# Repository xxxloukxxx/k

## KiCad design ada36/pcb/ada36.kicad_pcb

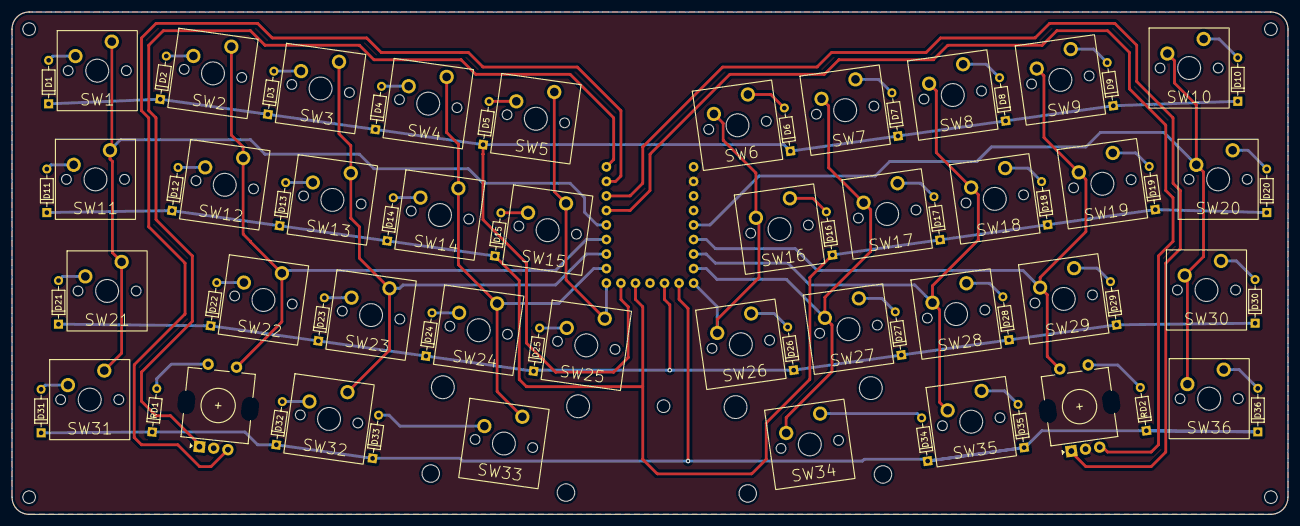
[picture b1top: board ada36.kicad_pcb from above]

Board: 2 copper layers, 223.1 x 87.8 mm, 82 parts (1 on the bottom side), 57 nets.

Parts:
D1, D2, D3, D4, D5, D6, D7, D8, D9, D10, D11, D12, D13, D14, D15, D16, D17, D18, D19, D20, D21, D22, D23, D24, D25, D26, D27, D28, D29, D30, D31, D32, D33, D34, D35, D36: DIODE; Diode
H1, H2, H3, H4, H5: MountingHole; MountingHole_2.2mm_M2
R1, R2: EC11-MX-Alps; RotaryEncoder_EC11
RD1, RD2: DIODE; Diode
SW1, SW2, SW3, SW4, SW5, SW6, SW7, SW8, SW9, SW10, SW11, SW12, SW13, SW14, SW15, SW16, SW17, SW18, SW19, SW20, SW21, SW22, SW23, SW24, SW25, SW26, SW27, SW28, SW29, SW30, SW31, SW32, SW35, SW36: key; MX-5pin
SW33, SW34: key; MX-5pin_stab_rev
U1: RP2040

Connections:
GND: R1.C, R2.C, U1.21
unnamed: D1.2, SW1.2
unnamed: D2.2, SW2.2
unnamed: D3.2, SW3.2
unnamed: D4.2, SW4.2
unnamed: D5.2, SW5.2
unnamed: D6.2, SW6.1
unnamed: D7.2, SW7.1
unnamed: D8.2, SW8.1
unnamed: D9.2, SW9.1
unnamed: D10.2, SW10.1
unnamed: D11.2, SW11.2
unnamed: D12.2, SW12.2
unnamed: D13.2, SW13.2
unnamed: D14.2, SW14.2
unnamed: D15.2, SW15.2
unnamed: D16.2, SW16.1
unnamed: D17.2, SW17.1
unnamed: D18.2, SW18.1
unnamed: D19.2, SW19.1
unnamed: D20.2, SW20.1
unnamed: D21.2, SW21.2
unnamed: D22.2, SW22.2
unnamed: D23.2, SW23.2
unnamed: D24.2, SW24.2
unnamed: D25.2, SW25.2
unnamed: D26.2, SW26.1
unnamed: D27.2, SW27.1
unnamed: D28.2, SW28.1
unnamed: D29.2, SW29.1
unnamed: D30.2, SW30.1
unnamed: D31.2, SW31.2
unnamed: D32.2, SW32.2
unnamed: D33.2, SW33.2
unnamed: D34.2, SW34.1
unnamed: D35.2, SW35.1
unnamed: D36.2, SW36.1
unnamed: R1.1, RD1.2
unnamed: R1.A, U1.0
unnamed: R1.B, U1.1
unnamed: R2.2, RD2.2
unnamed: R2.A, U1.2
unnamed: R2.B, U1.3
c0: SW1.1, SW11.1, SW21.1, SW31.1, U1.4
c1: R1.2, SW2.1, SW12.1, SW22.1, U1.5
c2: SW3.1, SW13.1, SW23.1, SW32.1, U1.6
c3: SW4.1, SW14.1, SW24.1, SW33.1, U1.7
c4: SW5.1, SW15.1, SW25.1, U1.8
c5: SW6.2, SW16.2, SW26.2, U1.14
c6: SW7.2, SW17.2, SW27.2, SW34.2, U1.15
c7: SW8.2, SW18.2, SW28.2, SW35.2, U1.16
c8: R2.1, SW9.2, SW19.2, SW29.2, U1.17
c9: SW10.2, SW20.2, SW30.2, SW36.2, U1.18
l0: D31.1, D32.1, D33.1, D34.1, D35.1, D36.1, RD1.1, RD2.1, U1.13
l1: D21.1, D22.1, D23.1, D24.1, D25.1, D26.1, D27.1, D28.1, D29.1, D30.1, U1.12
l2: D11.1, D12.1, D13.1, D14.1, D15.1, D16.1, D17.1, D18.1, D19.1, D20.1, U1.10
l3: D1.1, D2.1, D3.1, D4.1, D5.1, D6.1, D7.1, D8.1, D9.1, D10.1, U1.9

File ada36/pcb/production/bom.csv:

Designator,Footprint,Quantity,Value,LCSC Part #
"D1, D10, D11, D12, D13, D14, D15, D16, D17, D18, D19, D2, D20, D21, D22, D23, D24, D25, D26, D27, D28, D29, D3, D30, D31, D32, D33, D34, D35, D36, D4, D5, D6, D7, D8, D9, RD1, RD2",Diode,38,Diode,
"H1, H2, H3, H4, H5",MountingHole_2.2mm_M2,5,MountingHole,
"R1, R2",RotaryEncoder_EC11,2,EC11-MX-Alps,
"SW1, SW10, SW11, SW12, SW13, SW14, SW15, SW16, SW17, SW18, SW19, SW2, SW20, SW21, SW22, SW23, SW24, SW25, SW26, SW27, SW28, SW29, SW3, SW30, SW31, SW32, SW35, SW36, SW4, SW5, SW6, SW7, SW8, SW9",MX-5pin,34,key,
"SW33, SW34",MX-5pin_stab_rev,2,key,
U1,RP2040,1,RP2040,

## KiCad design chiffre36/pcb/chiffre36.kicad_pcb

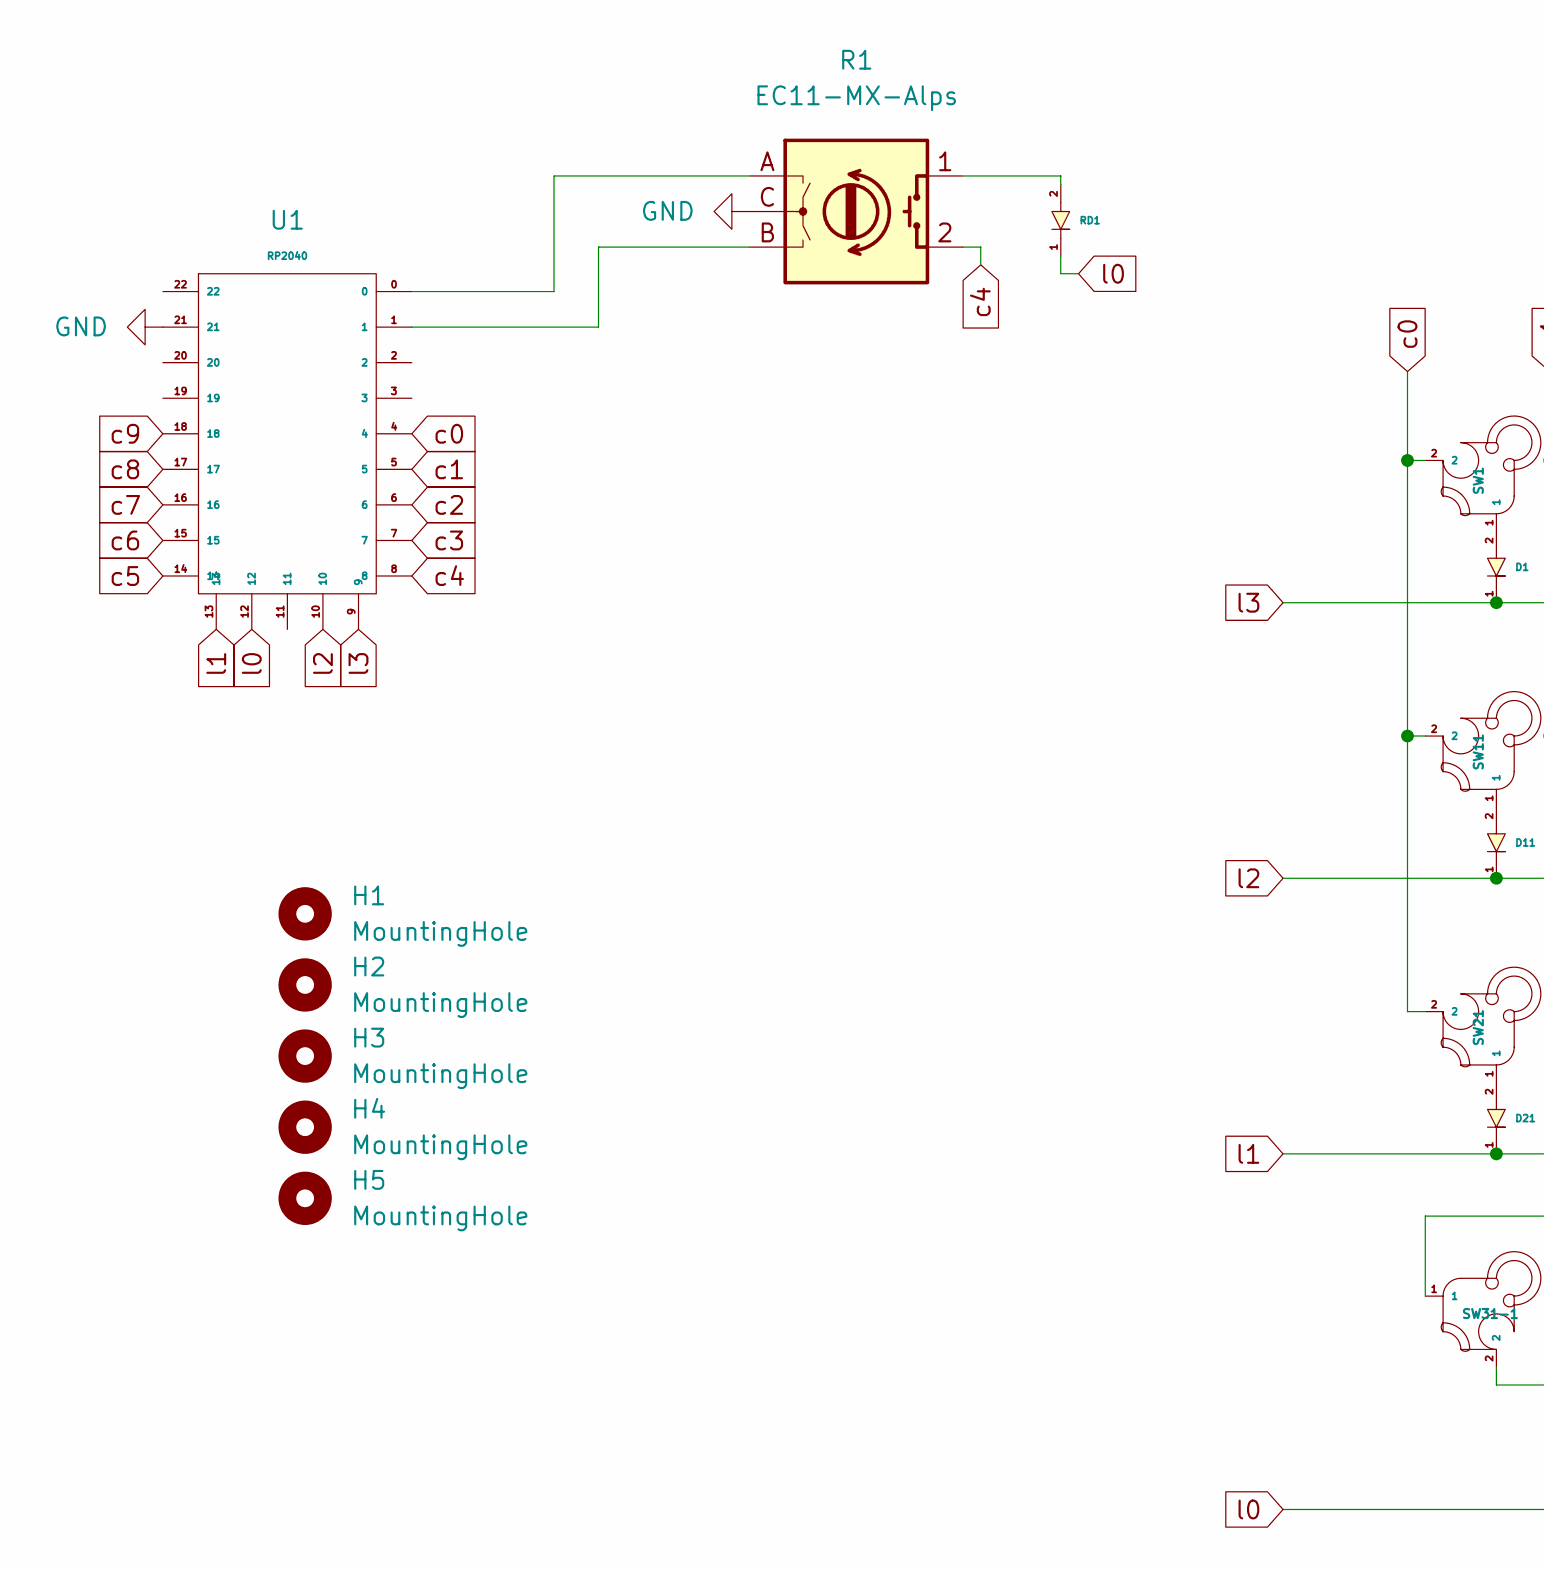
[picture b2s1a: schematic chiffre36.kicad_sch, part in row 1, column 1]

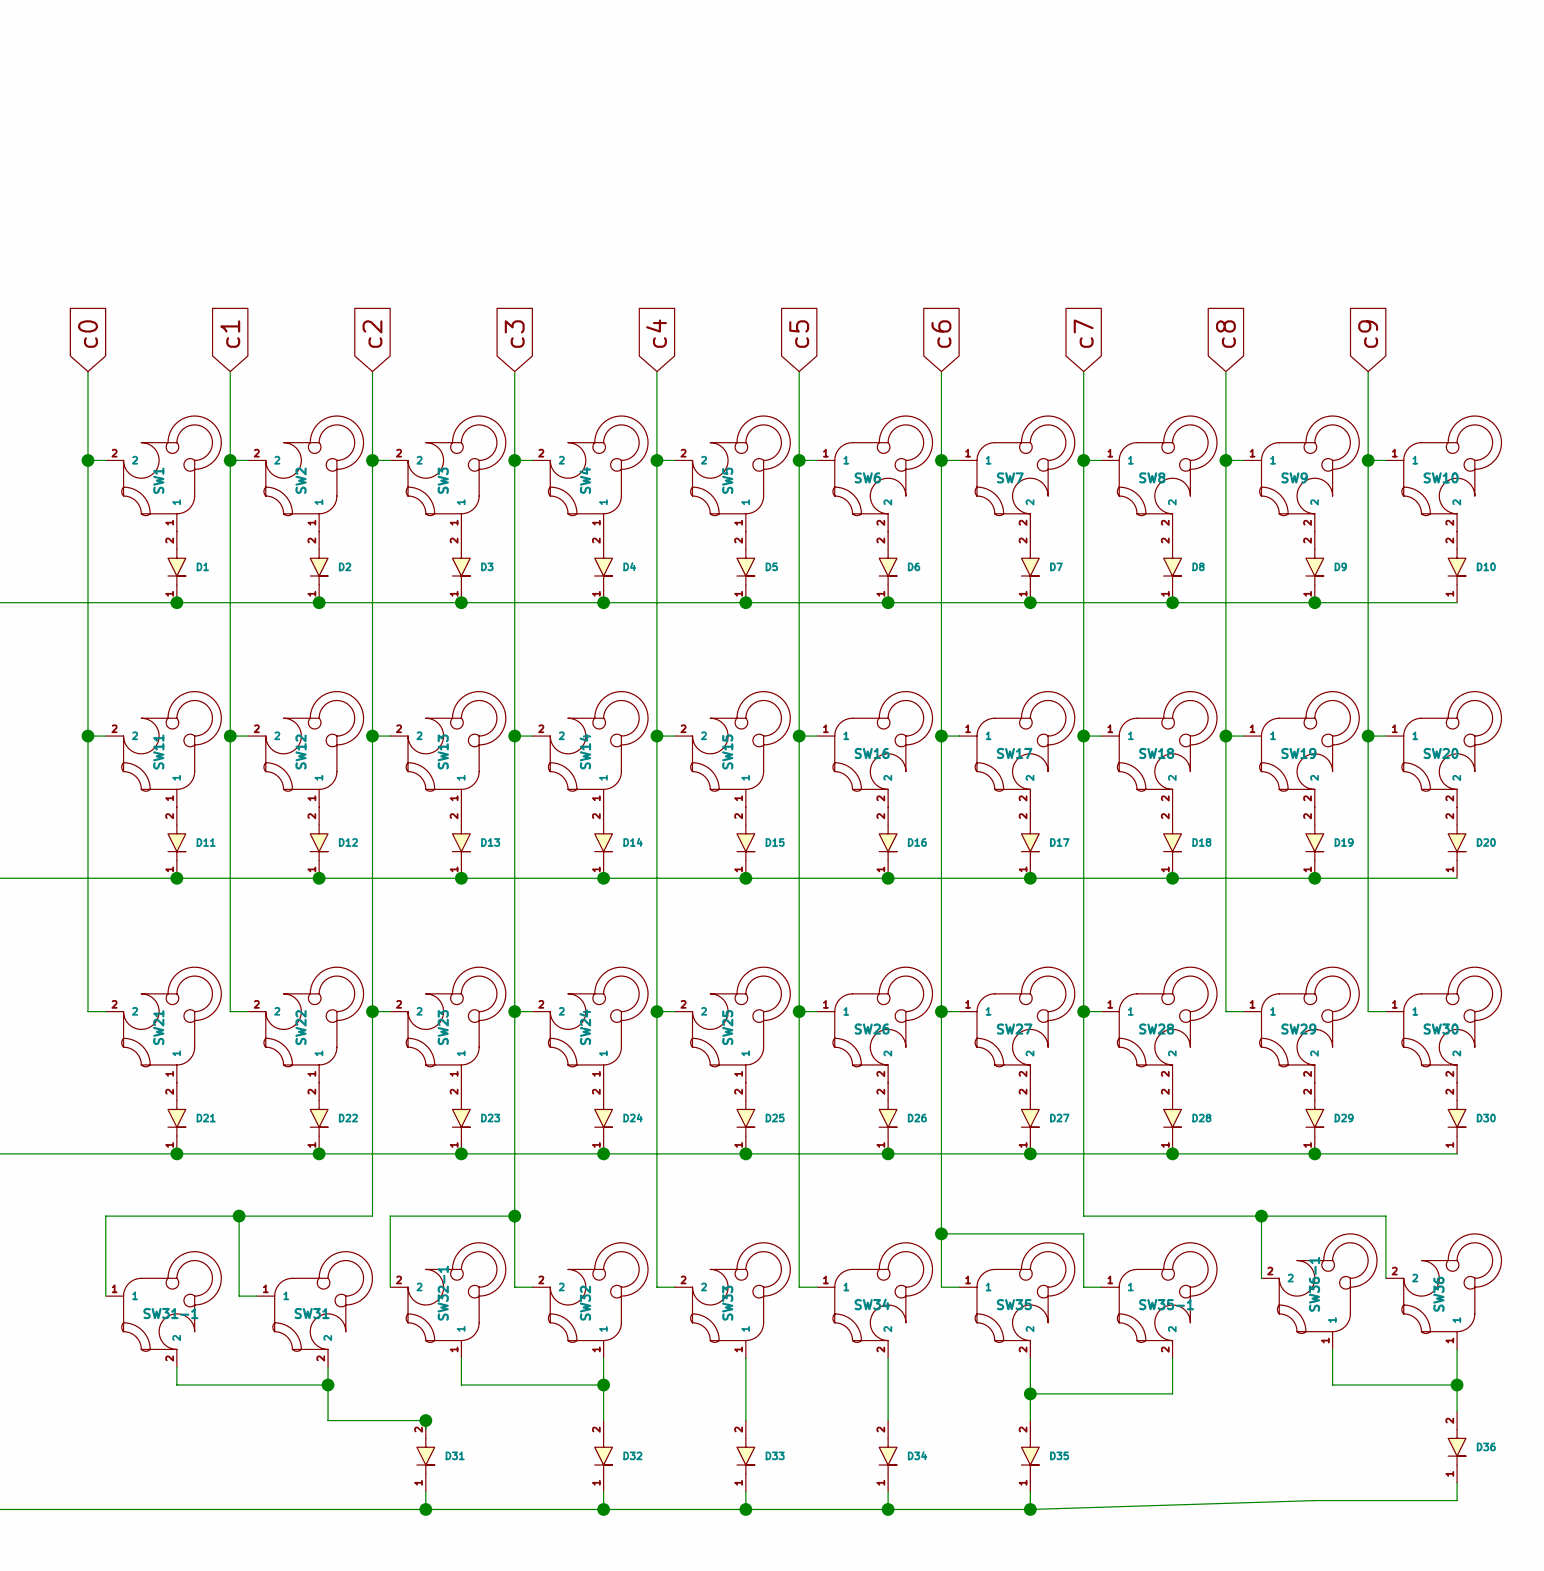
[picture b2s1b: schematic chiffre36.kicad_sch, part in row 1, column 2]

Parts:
D1, D2, D3, D4, D5, D6, D7, D8, D9, D10, D11, D12, D13, D14, D15, D16, D17, D18, D19, D20, D21, D22, D23, D24, D25, D26, D27, D28, D29, D30, D31, D32, D33, D34, D35, D36: Diode
H1, H2, H3, H4, H5: MountingHole; MountingHole_2.2mm_M2
R1: EC11-MX-Alps; RotaryEncoder_EC11
RD1: Diode
SW1, SW2, SW3, SW4, SW5, SW6, SW7, SW8, SW9, SW10, SW11, SW12, SW13, SW14, SW15, SW16, SW17, SW18, SW19, SW20, SW21, SW22, SW23, SW24, SW25, SW26, SW27, SW28, SW29, SW30, SW31, SW31-1, SW32, SW32-1, SW33, SW34, SW35, SW35-1, SW36, SW36-1: key; MX-5pin
U1: RP2040

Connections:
GND: R1.C, U1.21
unnamed: D1.2, SW1.1
unnamed: D2.2, SW2.1
unnamed: D3.2, SW3.1
unnamed: D4.2, SW4.1
unnamed: D5.2, SW5.1
unnamed: D6.2, SW6.2
unnamed: D7.2, SW7.2
unnamed: D8.2, SW8.2
unnamed: D9.2, SW9.2
unnamed: D10.2, SW10.2
unnamed: D11.2, SW11.1
unnamed: D12.2, SW12.1
unnamed: D13.2, SW13.1
unnamed: D14.2, SW14.1
unnamed: D15.2, SW15.1
unnamed: D16.2, SW16.2
unnamed: D17.2, SW17.2
unnamed: D18.2, SW18.2
unnamed: D19.2, SW19.2
unnamed: D20.2, SW20.2
unnamed: D21.2, SW21.1
unnamed: D22.2, SW22.1
unnamed: D23.2, SW23.1
unnamed: D24.2, SW24.1
unnamed: D25.2, SW25.1
unnamed: D26.2, SW26.2
unnamed: D27.2, SW27.2
unnamed: D28.2, SW28.2
unnamed: D29.2, SW29.2
unnamed: D30.2, SW30.2
unnamed: D31.2, SW31.2, SW31-1.2
unnamed: D32.2, SW32.1, SW32-1.1
unnamed: D33.2, SW33.1
unnamed: D34.2, SW34.2
unnamed: D35.2, SW35.2, SW35-1.2
unnamed: D36.2, SW36.1, SW36-1.1
unnamed: R1.1, RD1.2
unnamed: R1.A, U1.0
unnamed: R1.B, U1.1
c0: SW1.2, SW11.2, SW21.2, U1.4
c1: SW2.2, SW12.2, SW22.2, U1.5
c2: SW3.2, SW13.2, SW23.2, SW31.1, SW31-1.1, U1.6
c3: SW4.2, SW14.2, SW24.2, SW32.2, SW32-1.2, U1.7
c4: R1.2, SW5.2, SW15.2, SW25.2, SW33.2, U1.8
c5: SW6.1, SW16.1, SW26.1, SW34.1, U1.14
c6: SW7.1, SW17.1, SW27.1, SW35.1, SW35-1.1, U1.15
c7: SW8.1, SW18.1, SW28.1, SW36.2, SW36-1.2, U1.16
c8: SW9.1, SW19.1, SW29.1, U1.17
c9: SW10.1, SW20.1, SW30.1, U1.18
l0: D31.1, D32.1, D33.1, D34.1, D35.1, D36.1, RD1.1, U1.12
l1: D21.1, D22.1, D23.1, D24.1, D25.1, D26.1, D27.1, D28.1, D29.1, D30.1, U1.13
l2: D11.1, D12.1, D13.1, D14.1, D15.1, D16.1, D17.1, D18.1, D19.1, D20.1, U1.10
l3: D1.1, D2.1, D3.1, D4.1, D5.1, D6.1, D7.1, D8.1, D9.1, D10.1, U1.9

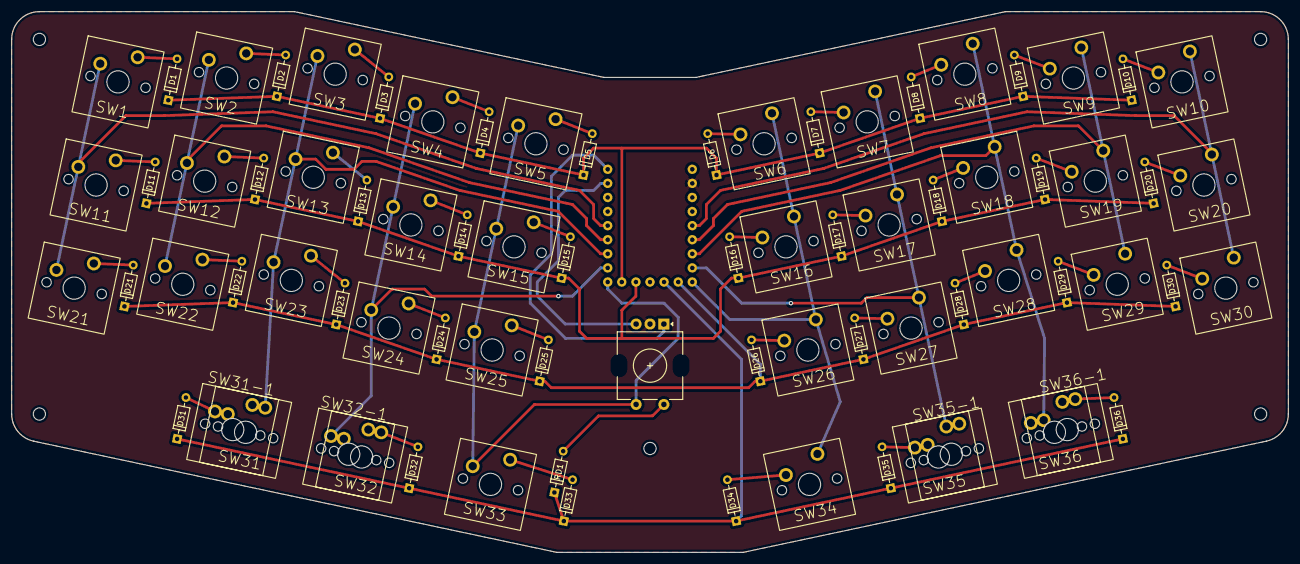
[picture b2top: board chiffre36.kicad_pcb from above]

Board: 2 copper layers, 230.1 x 97.5 mm, 84 parts (1 on the bottom side), 54 nets.

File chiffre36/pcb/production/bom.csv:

Designator,Footprint,Quantity,Value,LCSC Part #
"D1, D10, D11, D12, D13, D14, D15, D16, D17, D18, D19, D2, D20, D21, D22, D23, D24, D25, D26, D27, D28, D29, D3, D30, D31, D32, D33, D34, D35, D36, D4, D5, D6, D7, D8, D9, RD1",Diode,37,Diode,
"H1, H2, H3, H4, H5",MountingHole_2.2mm_M2,5,MountingHole,
R1,RotaryEncoder_EC11,1,EC11-MX-Alps,
"SW1, SW10, SW11, SW12, SW13, SW14, SW15, SW16, SW17, SW18, SW19, SW2, SW20, SW21, SW22, SW23, SW24, SW25, SW26, SW27, SW28, SW29, SW3, SW30, SW31, SW31-1, SW32, SW32-1, SW33, SW34, SW35, SW35-1, SW36, SW36-1, SW4, SW5, SW6, SW7, SW8, SW9",MX-5pin,40,key,
U1,RP2040,1,RP2040,
